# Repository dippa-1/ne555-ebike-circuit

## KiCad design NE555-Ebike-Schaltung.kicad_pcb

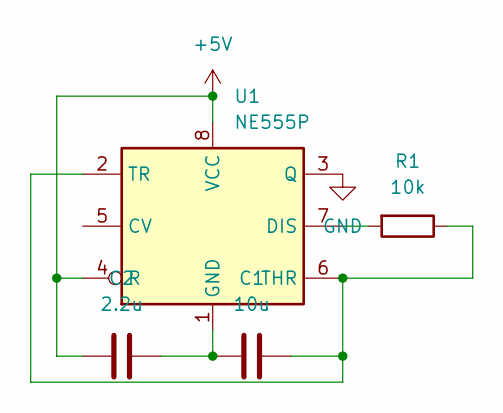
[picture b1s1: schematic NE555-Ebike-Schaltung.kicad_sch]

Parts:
C1: 10u; CP_Radial_D8.0mm_P2.50mm
C2: 2.2u; CP_Radial_D8.0mm_P2.50mm
R1: 10k; R_Axial_DIN0207_L6.3mm_D2.5mm_P10.16mm_Horizontal
U1: NE555P; DIP-8_W7.62mm

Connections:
+5V: C2.1, U1.4 (R), U1.8 (VCC)
GND: U1.3 (Q)
unnamed: C1.1, C2.2, U1.1 (GND)
unnamed: C1.2, R1.1, U1.2 (TR), U1.6 (THR)
unnamed: R1.2, U1.7 (DIS)

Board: 2 copper layers, 4 parts (0 on the bottom side), 4 nets, no tracks yet.

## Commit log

2022-08-05 initial files
2022-08-05 add first dsn test
